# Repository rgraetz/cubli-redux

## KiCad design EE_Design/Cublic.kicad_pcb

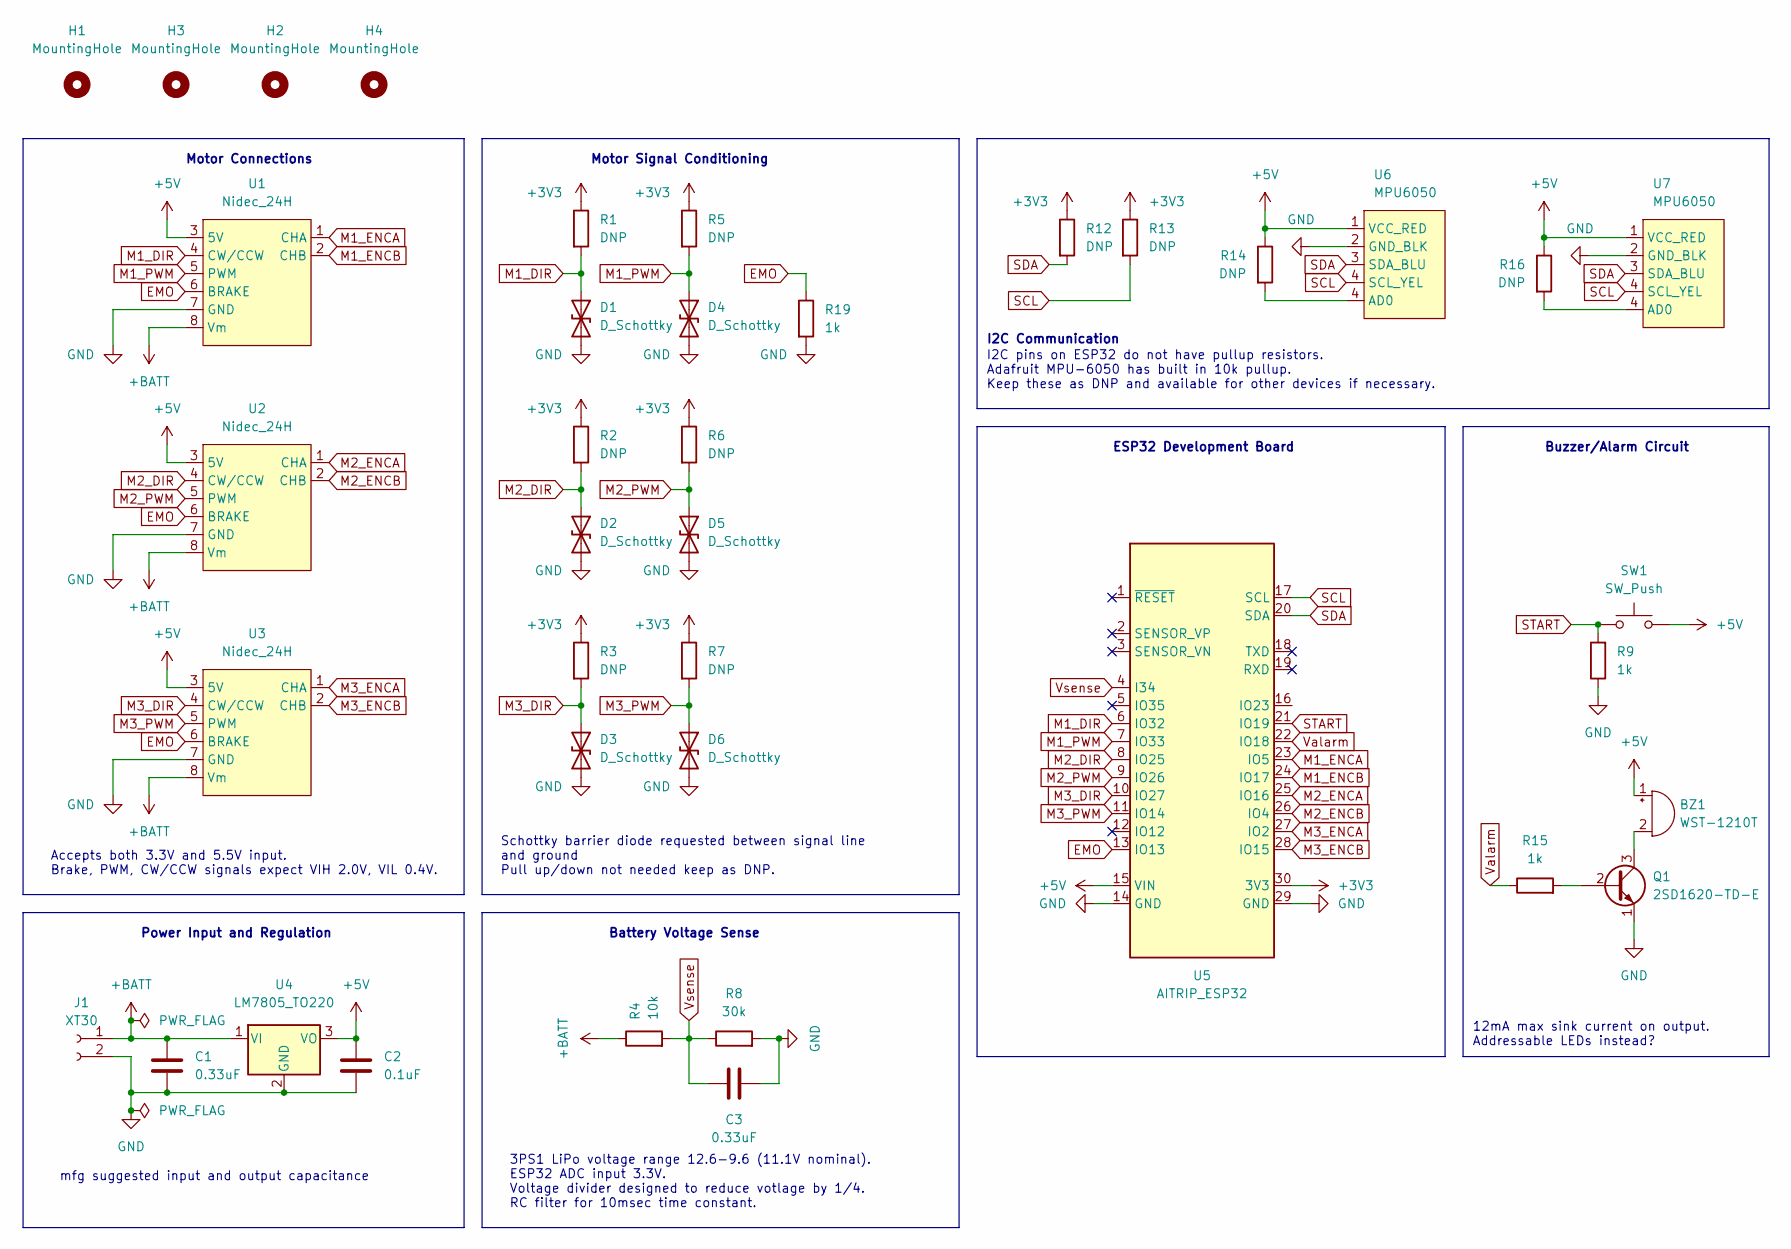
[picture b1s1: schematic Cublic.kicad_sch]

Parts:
BZ1: WST-1210T; Buzzer_12x9.5RM7.6
C1, C3: 0.33uF; C_0603_1608Metric_Pad1.08x0.95mm_HandSolder
C2: 0.1uF; C_0603_1608Metric_Pad1.08x0.95mm_HandSolder
D1, D2, D3, D4, D5, D6: D_Schottky; D_0603_1608Metric_Pad1.05x0.95mm_HandSolder; MPN SP1103C-01UTG
H1, H2, H3, H4: MountingHole; MountingHole_3.2mm_M3
J1: XT30; XT30PW_M
Q1: 2SD1620-TD-E; TO-243AA
R1, R2, R3, R5, R6, R7, R12, R13, R14, R16: DNP; R_0603_1608Metric_Pad0.98x0.95mm_HandSolder
R4: 10k; R_0603_1608Metric_Pad0.98x0.95mm_HandSolder
R8: 30k; R_0603_1608Metric_Pad0.98x0.95mm_HandSolder
R9, R15, R19: 1k; R_0603_1608Metric_Pad0.98x0.95mm_HandSolder
SW1: SW_Push; PinHeader_1x02_P2.54mm_Vertical
U1, U2, U3: Nidec_24H; PinHeader_1x08_P2.54mm_StrainRelief
U4: LM7805_TO220; TO-220-3_Horizontal_TabDown
U5: AITRIP_ESP32
U6, U7: MPU6050; Pinheader_1x05_P2.54mm_StrainRelief

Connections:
+3V3: R1.1, R2.1, R3.1, R5.1, R6.1, R7.1, R12.1, R13.1, U5.30 (3V3)
+5V: BZ1.1 (-), C2.1, R14.1, R16.1, SW1.2, U1.3 (5V), U2.3 (5V), U3.3 (5V), U4.3 (VO), U5.15 (VIN), U6.1 (VCC_RED), U7.1 (VCC_RED)
+BATT: C1.1, J1.1, R4.1, U1.8 (Vm), U2.8 (Vm), U3.8 (Vm), U4.1 (VI)
EMO: R19.1, U1.6 (BRAKE), U2.6 (BRAKE), U3.6 (BRAKE), U5.13 (IO13)
GND: C1.2, C2.2, C3.2, D1.2 (A2), D2.2 (A2), D3.2 (A2), D4.2 (A2), D5.2 (A2), D6.2 (A2), J1.2, Q1.1 (E), R8.2, R9.1, R19.2, U1.7 (GND), U2.7 (GND), U3.7 (GND), U4.2 (GND), U5.14 (GND), U5.29 (GND), U6.2 (GND_BLK), U7.2 (GND_BLK)
M1_DIR: D1.1 (A1), R1.2, U1.4 (CW/CCW), U5.6 (IO32)
M1_ENCA: U1.1 (CHA), U5.23 (IO5)
M1_ENCB: U1.2 (CHB), U5.24 (IO17)
M1_PWM: D4.1 (A1), R5.2, U1.5 (PWM), U5.7 (IO33)
M2_DIR: D2.1 (A1), R2.2, U2.4 (CW/CCW), U5.8 (IO25)
M2_ENCA: U2.1 (CHA), U5.25 (IO16)
M2_ENCB: U2.2 (CHB), U5.26 (IO4)
M2_PWM: D5.1 (A1), R6.2, U2.5 (PWM), U5.9 (IO26)
M3_DIR: D3.1 (A1), R3.2, U3.4 (CW/CCW), U5.10 (IO27)
M3_ENCA: U3.1 (CHA), U5.27 (IO2)
M3_ENCB: U3.2 (CHB), U5.28 (IO15)
M3_PWM: D6.1 (A1), R7.2, U3.5 (PWM), U5.11 (IO14)
unnamed: BZ1.2 (+), Q1.3 (C)
unnamed: Q1.2 (B), R15.2
SDA: R12.2, U5.20 (SDA), U6.3 (SDA_BLU), U7.3 (SDA_BLU)
START: R9.2, SW1.1, U5.21 (IO19)
Valarm: R15.1, U5.22 (IO18)
Vsense: C3.1, R4.2, R8.1, U5.4 (I34)

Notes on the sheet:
Accepts both 3.3V and 5.5V input. Brake, PWM, CW/CCW signals expect VIH 2.0V, VIL 0.4V.
Motor Signal Conditioning
ESP32 Development Board
12mA max sink current on output. Addressable LEDs instead?
Buzzer/Alarm Circuit
mfg suggested input and output capacitance
Power Input and Regulation
I2C pins on ESP32 do not have pullup resistors. Adafruit MPU-6050 has built in 10k pullup. Keep these as DNP and available for other devices if necessary.
Schottky barrier diode requested between signal line and ground Pull up/down not needed keep as DNP.
Motor Connections
Battery Voltage Sense
I2C Communication
3PS1 LiPo voltage range 12.6-9.6 (11.1V nominal). ESP32 ADC input 3.3V. Voltage divider designed to reduce votlage by 1/4. RC filter for 10msec time constant.

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
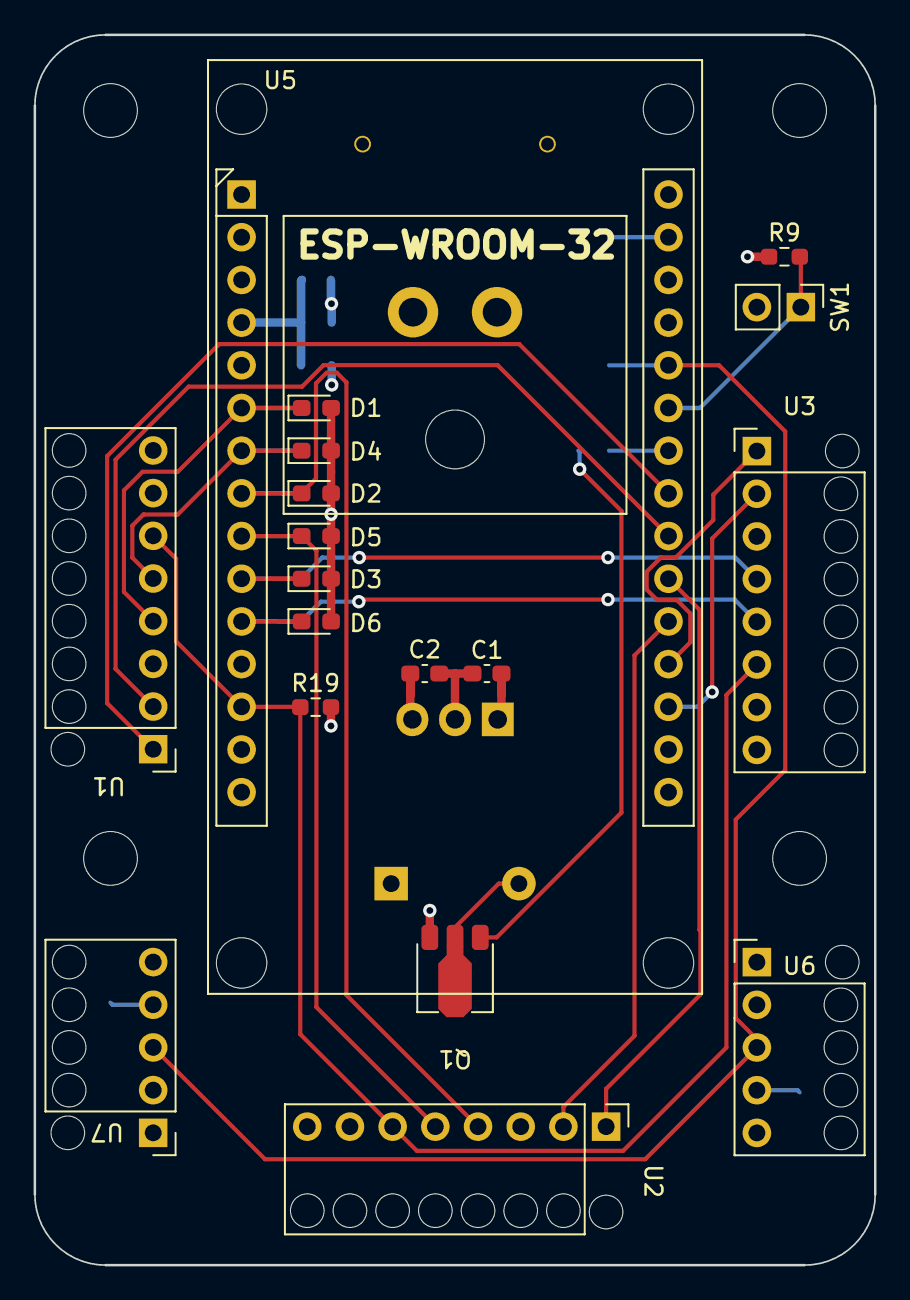
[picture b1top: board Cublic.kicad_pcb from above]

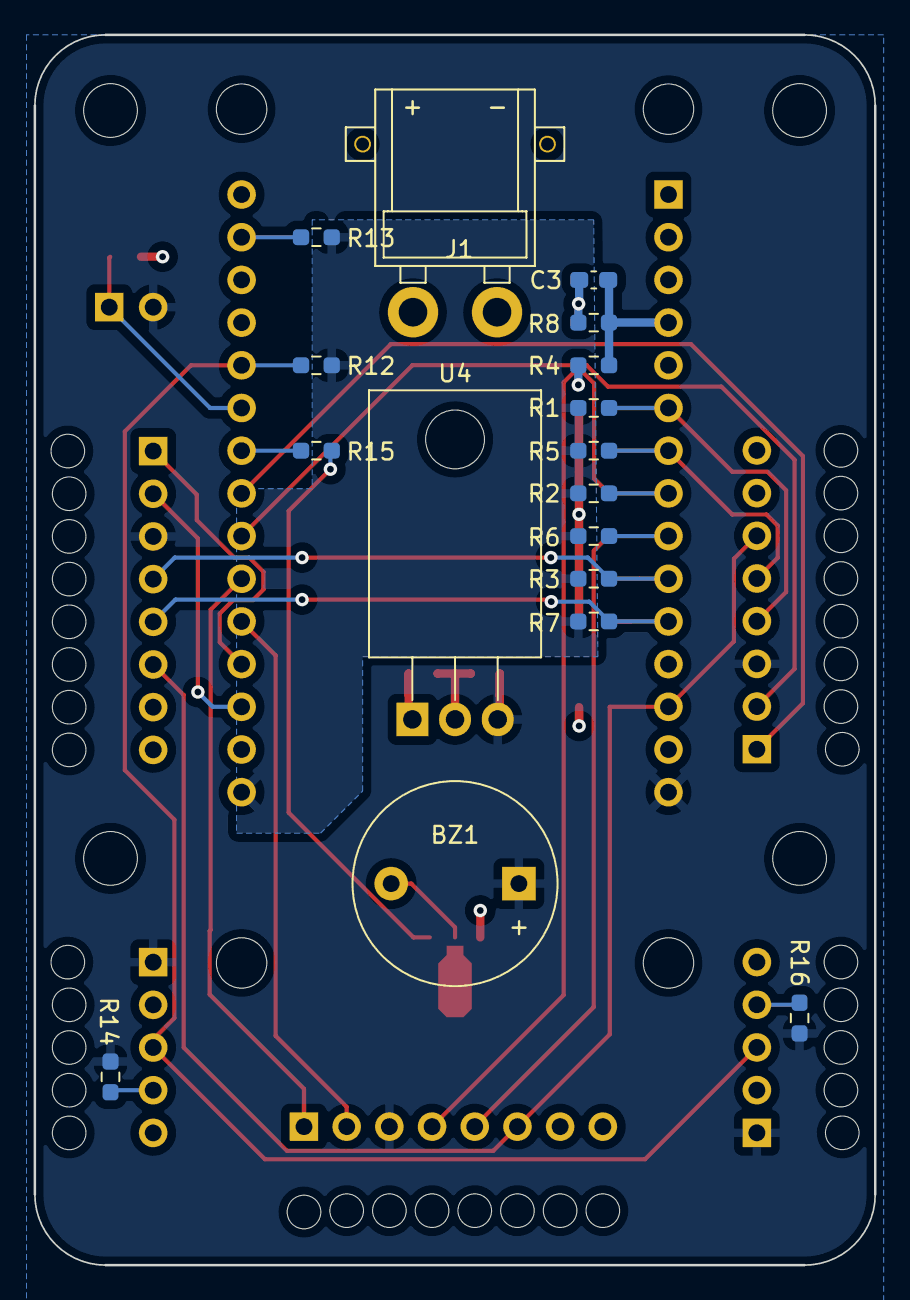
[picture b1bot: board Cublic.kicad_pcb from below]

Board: 4 copper layers, 50.0 x 73.2 mm, 39 parts (17 on the bottom side), 26 nets.

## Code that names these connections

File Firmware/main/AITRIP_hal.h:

#ifndef HAL_H
#define HAL_H

// GPIO DEFINITIONS
// motor direction outputs
#define M1_DIR_GPIO 32
#define M2_DIR_GPIO 25
#define M3_DIR_GPIO 27

// motor PWM speed control outputs
#define M1_PWM_GPIO 33
#define M2_PWM_GPIO 26
#define M3_PWM_GPIO 14

// motor encoder inputs
#define M1_CHA_GPIO 5
#define M1_CHB_GPIO 17

#define M2_CHA_GPIO 16
#define M2_CHB_GPIO 4

#define M3_CHA_GPIO 2
#define M3_CHB_GPIO 15

// brake
#define EMO_GPIO 13

// alarm
#define ALARM_GPIO 18

// MPU addr
#define MPU_ADDR 0x68

// buzzer/alarm
#define BUZZ_GPIO 18

// start switch
#define START_GPIO 19

// battery voltage measurement
#define BATT_AIN 34

//
#define CONTROL_RATE 100

#endif

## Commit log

2022-11-26 initial version - working IMU, control in progress
2022-11-28 single side control working but runs away
2022-12-03 smooth and stable single axis control
2022-12-05 Single edge control in fully cube config
    Leaky control = stable control
2022-12-07 before accel gryo control split
2022-12-07 parallel dual velocity/position loop
2022-12-08 nested position and velocity control
2022-12-11 initial EE design
2022-12-11 initial ME design
2022-12-11 support files
2022-12-11 corner balancing in progress
2022-12-15 corner balancing working but difficult start
2022-12-19 easy corner balancing working
